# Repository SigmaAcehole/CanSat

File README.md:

# CanSat
My Teensy code for CanSat using Arduino IDE.
My PCB schematics and design using AutoDesk Eagle.
This code fulfils the problem statement of CanSat 2020 organized by American Astronautical Society (AAS).

# Modules Used
1. Teensy 3.6 - Microcontroller board
2. MS5611 - Altitude/Pressure/Temperature
3. Adafruit Ultimate Breakout - GPS receiver
4. SPS30 - Dust Particle
5. MS4525DO - Air Speed
6. XBee S2C PRO - Telemetry

# PCB Design
|Board|Schematic|
|:---:|:-------:|
|||

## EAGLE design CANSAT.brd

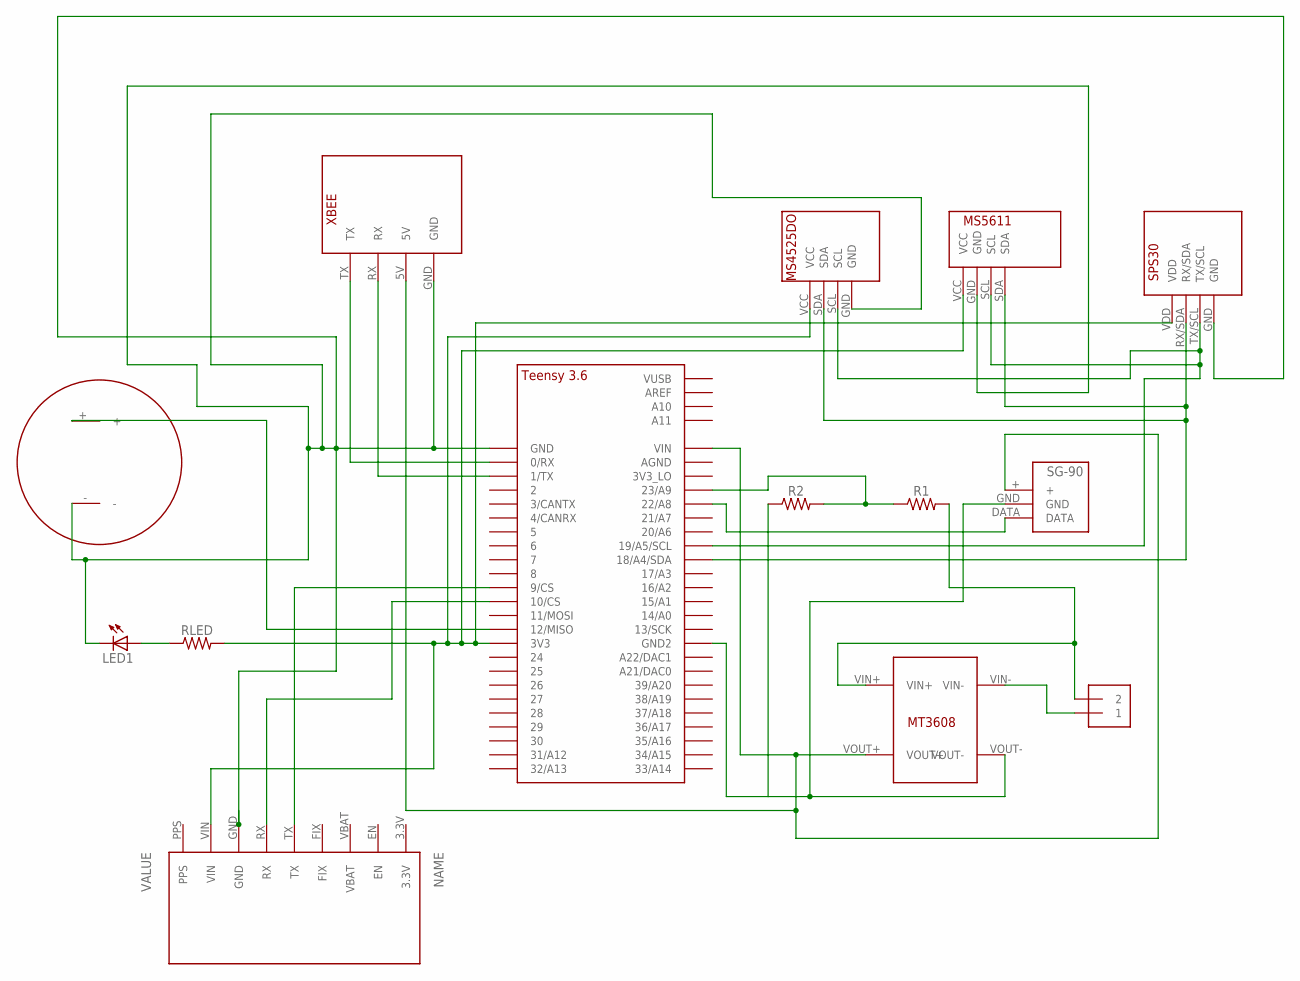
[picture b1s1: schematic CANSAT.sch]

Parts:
GPS1: ADAFRUITGPSBREAKOUT; ADAFRUITGPS
J1: 1X2-3.5MM
LED1: LED5MM
R1: 1.2K; AXIAL-0.3
R2: 2.5K; AXIAL-0.3
RLED: 220; AXIAL-0.3
U$1: MT3608
U$2: TEENSY_3.5/3.6_BASIC
U$3: XBEE-S2CPRO
U$4: MS4525DO
U$5: MS5611
U$6: SPS30
U$7: AL-3035; BUZZER
U$8: SG-90

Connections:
3V3: GPS1.VIN, RLED.P$2 (2), U$2.3V3, U$4.VCC, U$5.VCC, U$6.VDD
5V: U$1.VOUT+, U$2.VIN, U$3.5V, U$8.+
GND: GPS1.GND, LED1.K (C), U$2.GND, U$3.GND, U$4.GND, U$5.GND, U$6.GND, U$7.-
GND2: R2.P$1 (1), U$1.VOUT-, U$2.GND2, U$8.GND
unnamed: U$2.0/RX, U$3.TX
unnamed: LED1.A, RLED.P$1 (1)
unnamed: U$2.1/TX, U$3.RX
unnamed: J1.2, R1.P$2 (2), U$1.VIN+
unnamed: J1.1, U$1.VIN-
unnamed: U$2.22/A8, U$8.DATA
unnamed: U$2.12/MISO, U$7.+
unnamed: GPS1.TX, U$2.9/CS
unnamed: R1.P$1 (1), R2.P$2 (2), U$2.23/A9
unnamed: GPS1.RX, U$2.10/CS
SCL: U$2.19/A5/SCL, U$4.SCL, U$5.SCL, U$6.TX/SCL
SDA: U$2.18/A4/SDA, U$4.SDA, U$5.SDA, U$6.RX/SDA

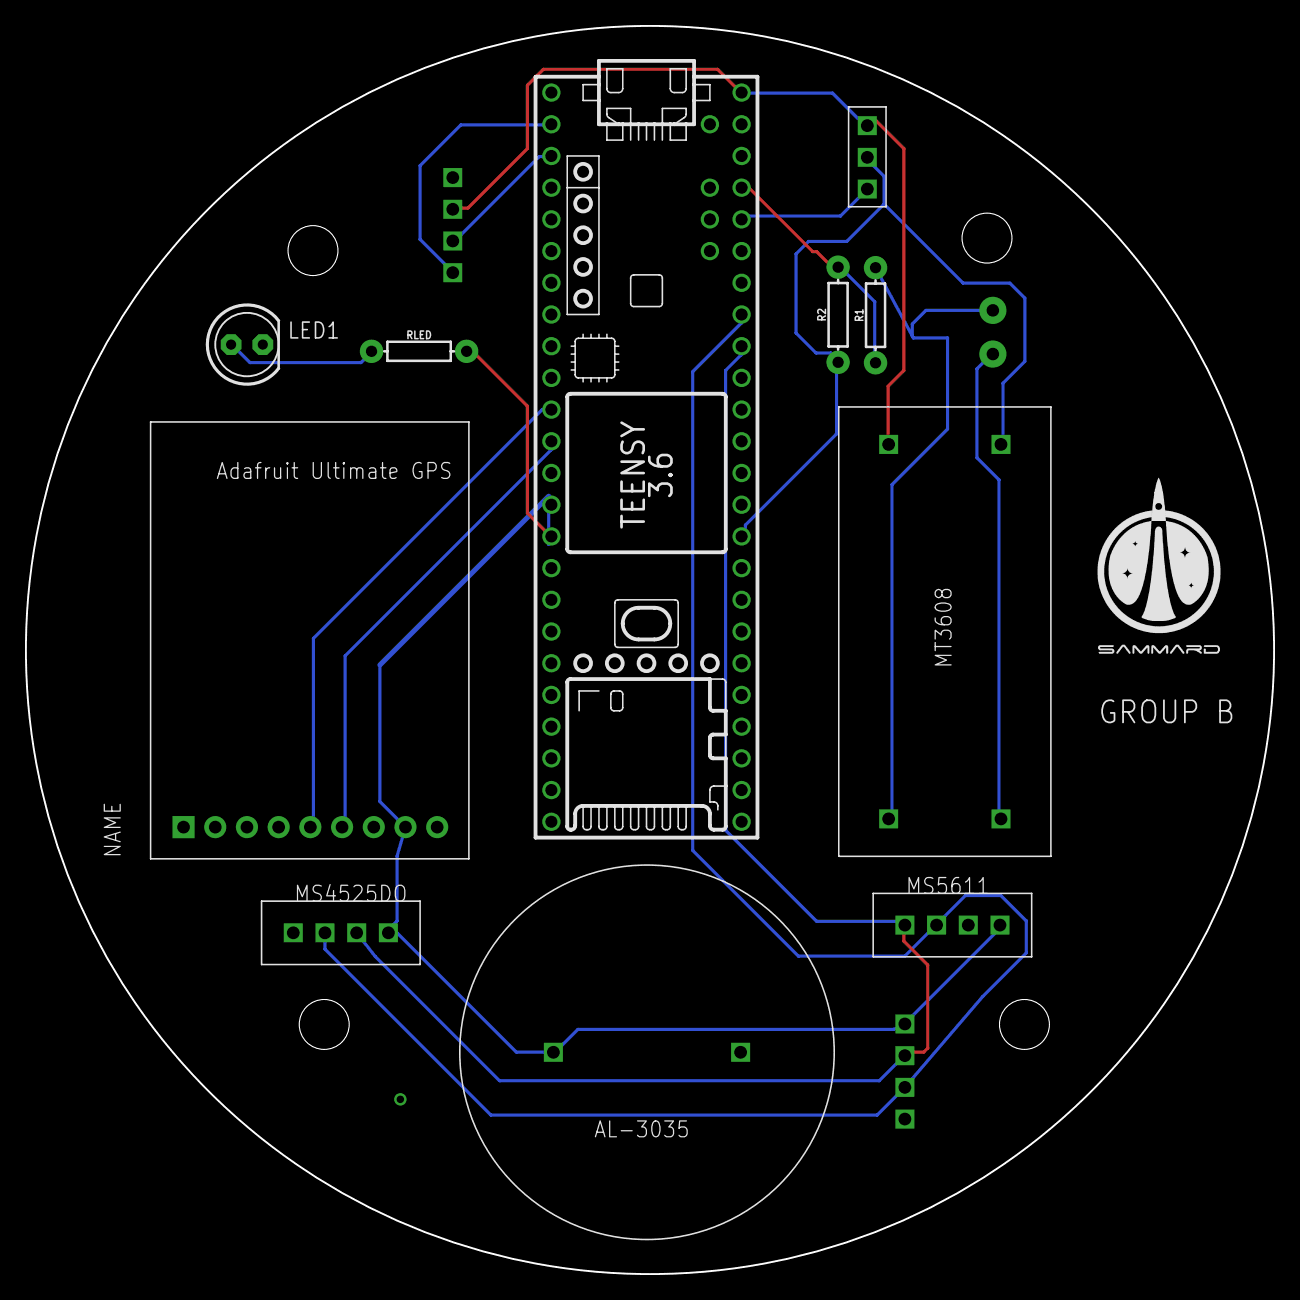
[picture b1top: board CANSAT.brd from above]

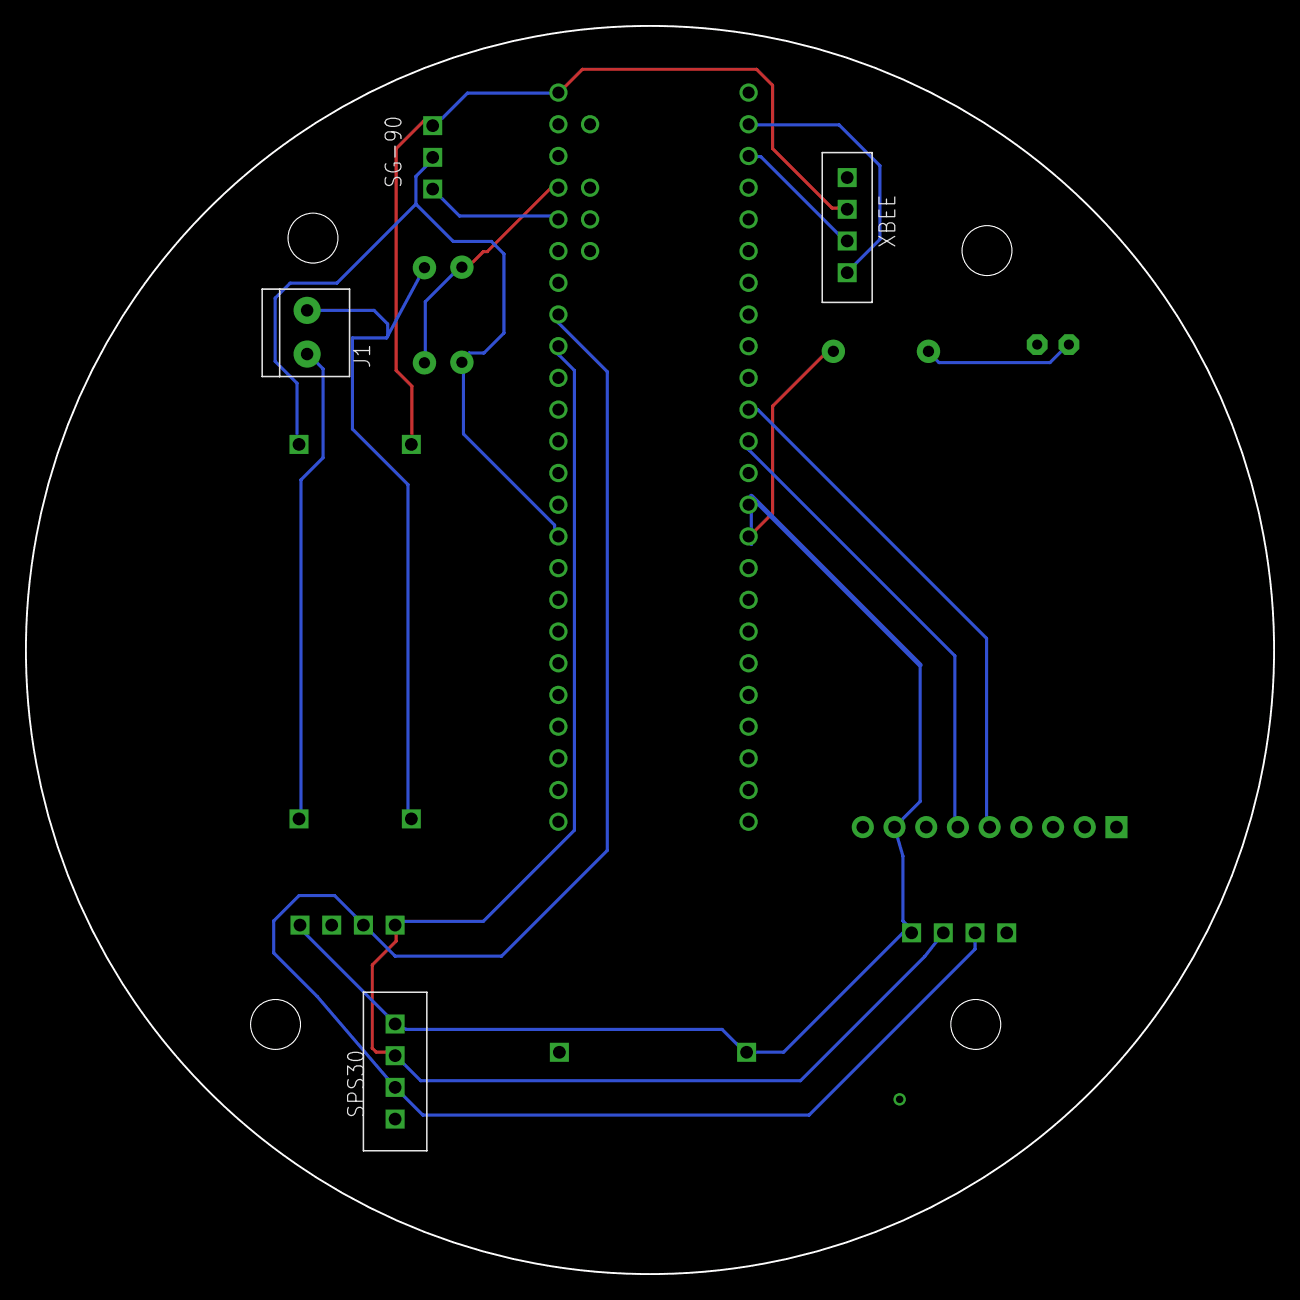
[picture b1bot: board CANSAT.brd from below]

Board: 2 copper layers, 100.0 x 100.0 mm, 14 parts (4 on the bottom side), 16 nets.

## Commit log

2020-05-27 Add files via upload
    Contains weight, power consumed and dimensions of major electronics used.
2020-11-06 Create CANSAT.b##
2021-07-05 final update

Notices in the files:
parts and their libraries:
SparkFun-Resistors: Licensing: Creative Commons ShareAlike 4.0 International - https://creativecommons.org/licenses/by-sa/4.0
